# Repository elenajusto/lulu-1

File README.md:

# lulu-1

# Mechanical
## Open Rocket View

## Physical Fully Assembled

# Electronic

## PCB Design 

### Architecture

### PCB Schematic 

## Perfboard Prototyping

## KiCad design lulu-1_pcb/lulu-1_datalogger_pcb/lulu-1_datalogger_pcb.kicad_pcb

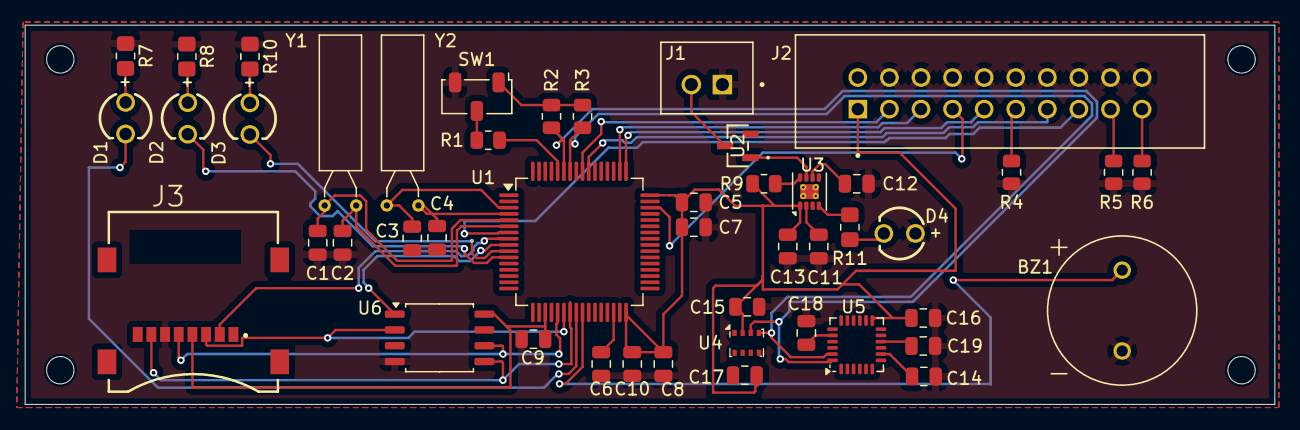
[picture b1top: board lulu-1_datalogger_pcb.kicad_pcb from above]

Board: 2 copper layers, 100.5 x 30.5 mm, 47 parts (0 on the bottom side), 39 nets.

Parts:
BZ1: Buzzer; XDCR_AT-1224-TWT-5V-2-R
C1, C2: 20pF; C_0805_2012Metric
C3, C4: 1.5pF; C_0805_2012Metric
C5, C7, C8, C9: 100 nF; C_0805_2012Metric
C6, C11, C13: 2.2uF; C_0805_2012Metric
C10, C14: 10nF; C_0805_2012Metric
C12: 33nF; C_0805_2012Metric
C15, C17: 100nf; C_0805_2012Metric
C16, C19: 0.1uF; C_0805_2012Metric
C18: 2.2nF; C_0805_2012Metric
D1, D2, D3, D4: LED; WL-TMRC_3MM
J1: B2B-XH-A; JST_B2B-XH-A
J2: SBH11-PBPC-D10-ST-BK; SULLINS_SBH11-PBPC-D10-ST-BK
J3: MEM2067-02-180-00-A_REVB; GCT_MEM2067-02-180-00-A_REVB
R1, R3: 10k; R_0805_2012Metric
R2, R4, R5, R6: 10K; R_0805_2012Metric
R7, R8, R10, R11: 100Ω; R_0805_2012Metric_Pad1.20x1.40mm_HandSolder
R9: 100k; R_0805_2012Metric
SW1: SW_Nidec_CAS-120A1; Nidec_Copal_CAS-120A
U1: STM32F401RETx; LQFP-64_10x10mm_P0.5mm
U2: BAT54LT1G; SOT-23-3_1P4X3P040_ONS
U3: LP3982ILD-3.3; WSON-8-1EP_3x2.5mm_P0.5mm_EP1.2x1.5mm_PullBack_ThermalVias
U4: BMP280; Bosch_LGA-8_2x2.5mm_P0.65mm_ClockwisePinNumbering
U5: MPU-6050; InvenSense_QFN-24_4x4mm_P0.5mm
U6: W25Q16JVSS; SOIC-8_5.23x5.23mm_P1.27mm
Y1: 25 Mhz; Crystal_AT310_D3.0mm_L10.0mm_Horizontal
Y2: 32 Khz; Crystal_AT310_D3.0mm_L10.0mm_Horizontal

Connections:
+3.3V: R2.2, R3.2, SW1.1 (C)
+3V3: C5.2, C7.2, C8.2, C9.2, C10.2, C13.1, C14.2, C15.2, C16.1, C17.2, J2.1, J2.2, J3.4 (VDD), R9.2, R11.1, U1.1 (VBAT), U1.19 (VDD), U1.32 (VDD), U1.48 (VDD), U1.64 (VDD), U3.1 (OUT), U3.4 (OUT), U4.2 (CSB), U4.6 (VDDIO), U4.8 (VDD), U5.8 (VLOGIC), U5.13 (VDD), U6.8 (VCC)
BUZZ: BZ1.P, U1.25 (PC5)
CS_FLASH: U1.9 (PC1), U6.1 (~CS)
CS_SD: J3.2 (CD/DAT3), U1.8 (PC0)
GND: BZ1.N, C1.1, C2.1, C3.1, C4.1, C5.1, C6.1, C7.1, C8.1, C9.1, C10.1, C11.2, C12.2, C13.2, C14.1, C15.1, C16.2, C17.1, C18.1, C19.2, D4.1 (K), J1.1, J2.4, J2.6, J2.8, J2.10, J2.12, J2.14, J2.16, J2.18, J2.20, J3.6 (VSS), R4.1, R5.1, R6.1, R7.1, R8.1, R10.1, SW1.3 (A), U1.12 (VSSA), U1.18 (VSS), U1.31 (VSS), U1.47 (VSS), U1.63 (VSS), U3.3 (GND), U4.1 (GND), U4.5 (SDO), U4.7 (GND), U5.18 (GND), U6.4 (GND)
JTCK_SWCLK: J2.9, U1.49 (PA14)
JTDI: J2.5, U1.50 (PA15)
JTDO_SWO: J2.13, U1.55 (PB3)
JTMS_SWDIO: J2.7, U1.46 (PA13)
JTRST: J2.3, U1.56 (PB4)
LED1: D3.2 (A), U1.10 (PC2)
LED2: D2.2 (A), U1.11 (PC3)
LED3: D1.2 (A), U1.24 (PC4)
NRST: J2.15, U1.7 (NRST)
unnamed: D1.1 (K), R7.2
unnamed: D2.1 (K), R8.2
unnamed: D3.1 (K), R10.2
unnamed: D4.2 (A), R11.2
unnamed: J2.11, R4.2
unnamed: J2.17, R5.2
unnamed: J2.19, R6.2
unnamed: R1.1, SW1.2 (B)
unnamed: R1.2, U1.60 (BOOT0)
unnamed: C3.2, U1.3 (PC14), Y2.2
unnamed: C4.2, U1.4 (PC15), Y2.1
unnamed: C1.2, U1.5 (PH0), Y1.2
unnamed: C2.2, U1.6 (PH1), Y1.1
unnamed: C6.2, U1.30 (VCAP1)
unnamed: C12.1, U3.6 (CC)
unnamed: R9.1, U3.8 (~FAULT)
unnamed: C18.2, U5.20 (CPOUT)
unnamed: C19.1, U5.10 (REGOUT)
PB6: R3.1, U1.58 (PB6), U4.4 (SCK), U5.23 (SCL)
PB7: R2.1, U1.59 (PB7), U4.3 (SDI), U5.24 (SDA)
SP1_MISO: J3.3 (CMD), U1.22 (PA6), U6.2 (DO(IO1))
SP1_MOSI: J3.7 (DAT0), U1.23 (PA7), U6.5 (DI(IO0))
SP1_SCK: J3.5 (CLK), U1.21 (PA5), U6.6 (CLK)
VBUS: C11.1, J1.2, U2.1 (ANODE), U2.3 (CATHODE), U3.2 (IN), U3.7 (~SHDN)

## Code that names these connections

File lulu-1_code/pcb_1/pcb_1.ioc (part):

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Mcu.Name=STM32F401R(D-E)Tx
Mcu.Package=LQFP64
Mcu.UserName=STM32F401RETx
PA11.Mode=Device_Only
PA11.Signal=USB_OTG_FS_DM
PA12.Mode=Device_Only
PA12.Signal=USB_OTG_FS_DP
PA13.Mode=JTAG_5_pins
PA13.Signal=SYS_JTMS-SWDIO
PA14.Mode=JTAG_5_pins
PA14.Signal=SYS_JTCK-SWCLK
PA15.Mode=JTAG_5_pins
PA15.Signal=SYS_JTDI
PA5.Mode=Full_Duplex_Master
PA5.Signal=SPI1_SCK
PA6.Mode=Full_Duplex_Master
PA6.Signal=SPI1_MISO
PA7.Mode=Full_Duplex_Master
PA7.Signal=SPI1_MOSI
PB3.Mode=JTAG_5_pins
PB3.Signal=SYS_JTDO-SWO
PB4.Mode=JTAG_5_pins
PB4.Signal=SYS_JTRST
PB6.Mode=I2C
PB6.Signal=I2C1_SCL
PB7.Mode=I2C
PB7.Signal=I2C1_SDA
PC0.GPIOParameters=GPIO_Label
PC0.GPIO_Label=CS_SD
PC0.Signal=GPIO_Output
PC1.GPIOParameters=GPIO_Label
PC1.GPIO_Label=CS_FLASH
PC1.Signal=GPIO_Output
PC14-OSC32_IN.Mode=LSE-External-Oscillator
PC14-OSC32_IN.Signal=RCC_OSC32_IN
PC15-OSC32_OUT.Mode=LSE-External-Oscillator
PC15-OSC32_OUT.Signal=RCC_OSC32_OUT
PC2.GPIOParameters=GPIO_Label
PC2.GPIO_Label=GPIO_LED1
PC2.Signal=GPIO_Output
PC3.GPIOParameters=GPIO_Label
PC3.GPIO_Label=GPIO_LED2
PC3.Signal=GPIO_Output
PC4.GPIOParameters=GPIO_Label
PC4.GPIO_Label=GPIO_LED3
PC4.Signal=GPIO_Output
PC5.GPIOParameters=GPIO_Label
PC5.GPIO_Label=GPIO_BUZZ
PC5.Signal=GPIO_Output
PH0\ -\ OSC_IN.Mode=HSE-External-Oscillator
PH0\ -\ OSC_IN.Signal=RCC_OSC_IN
PH1\ -\ OSC_OUT.Mode=HSE-External-Oscillator
PH1\ -\ OSC_OUT.Signal=RCC_OSC_OUT
RCC.HSE_VALUE=25000000
RCC.SYSCLKFreq_VALUE=16000000
board=custom

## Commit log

2024-10-05 Lulu-1 LPR OpenRocket sim based on physical measurements
2024-10-08 first iteration of datalogger pcb
2024-10-08 initialised stm32 project. initialised pinouts
2024-10-08 additional files
2024-10-08 remove metadata from stm32 from tracking
2024-10-08 removed .settings from stm32 from tracking
2024-10-08 fix gitingore
2024-10-08 deleted project
2024-10-08 reinit stm32 project
2024-10-08 initialised pins for SPI CS and added on schematic
2024-10-08 decoupling capactirs to i2c components as per datasheets
2024-10-09 updated openrocket values for avionics
2024-10-09 changed MOSI and MISO connection for flash chiP
2024-10-09 added 0805 footprints for resistors and capacitors
2024-10-15 Replaced footprint and symbol for USB with part that i am ordering
2024-10-15 tidy circuit
2024-10-15 more tidying
2024-10-18 imported and added hinged sd card with footprint
2024-10-18 removed usb-c from schematic
2024-10-18 re-imported JTAG connector with symbol and footprint from manufacturer
2024-10-18 reannotated schematic
2024-10-18 reorgansed schematic to be more cleaner
2024-10-18 label for SPI chip select pins and remvoed VBAT and merged with +3V3/VDD pins
2024-10-18 added reverse polarity protection diode
2024-10-18 added JST-XH connector for 18650 LiIon battery
2024-10-19 removed usb bus pins from mcu
2024-10-19 added continuity LED to voltage regulator output
2024-10-19 added programmable LEDs and buzzer to schematic and to .ioc file
2024-10-19 assigned footprint to continuity led
2024-10-19 assigned footprints to indictors
2024-10-19 something
2024-10-19 fixed LED polarity on schematic
2024-10-19 initial pcb layout
2024-10-19 added mounting holes
2024-10-21 finished initial traces. however errors in DRC to be resolved
2024-10-21 changed clearance to 0.15mm
2024-10-21 reduced minimum thermal spoke count to 1
2024-10-22 resolved all DRC errors
